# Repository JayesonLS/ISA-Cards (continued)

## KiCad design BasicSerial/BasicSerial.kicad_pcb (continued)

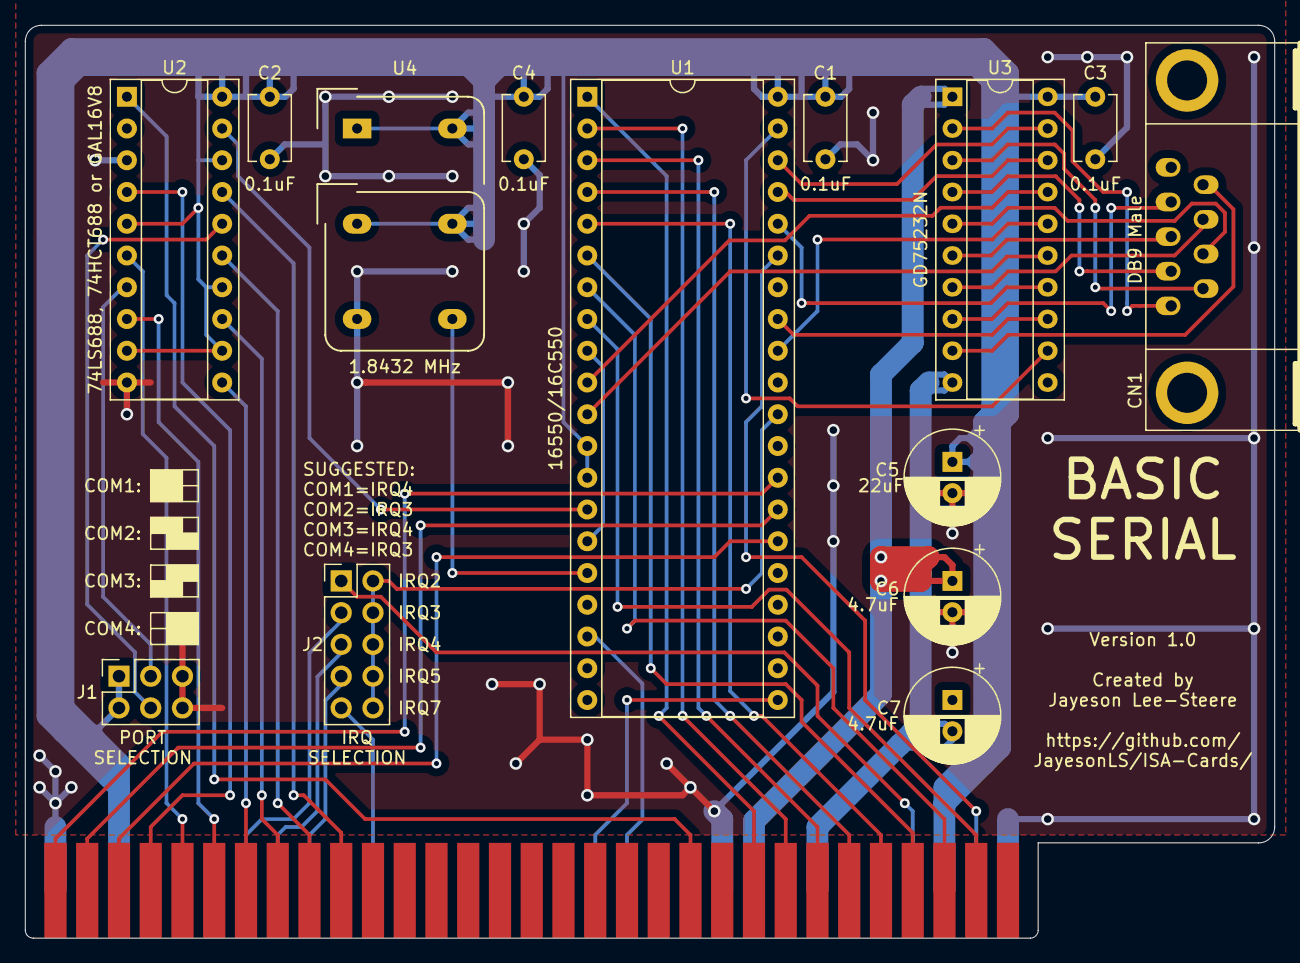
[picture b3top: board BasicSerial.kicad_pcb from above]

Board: 2 copper layers, 99.9 x 73.0 mm, 15 parts (0 on the bottom side), 53 nets.

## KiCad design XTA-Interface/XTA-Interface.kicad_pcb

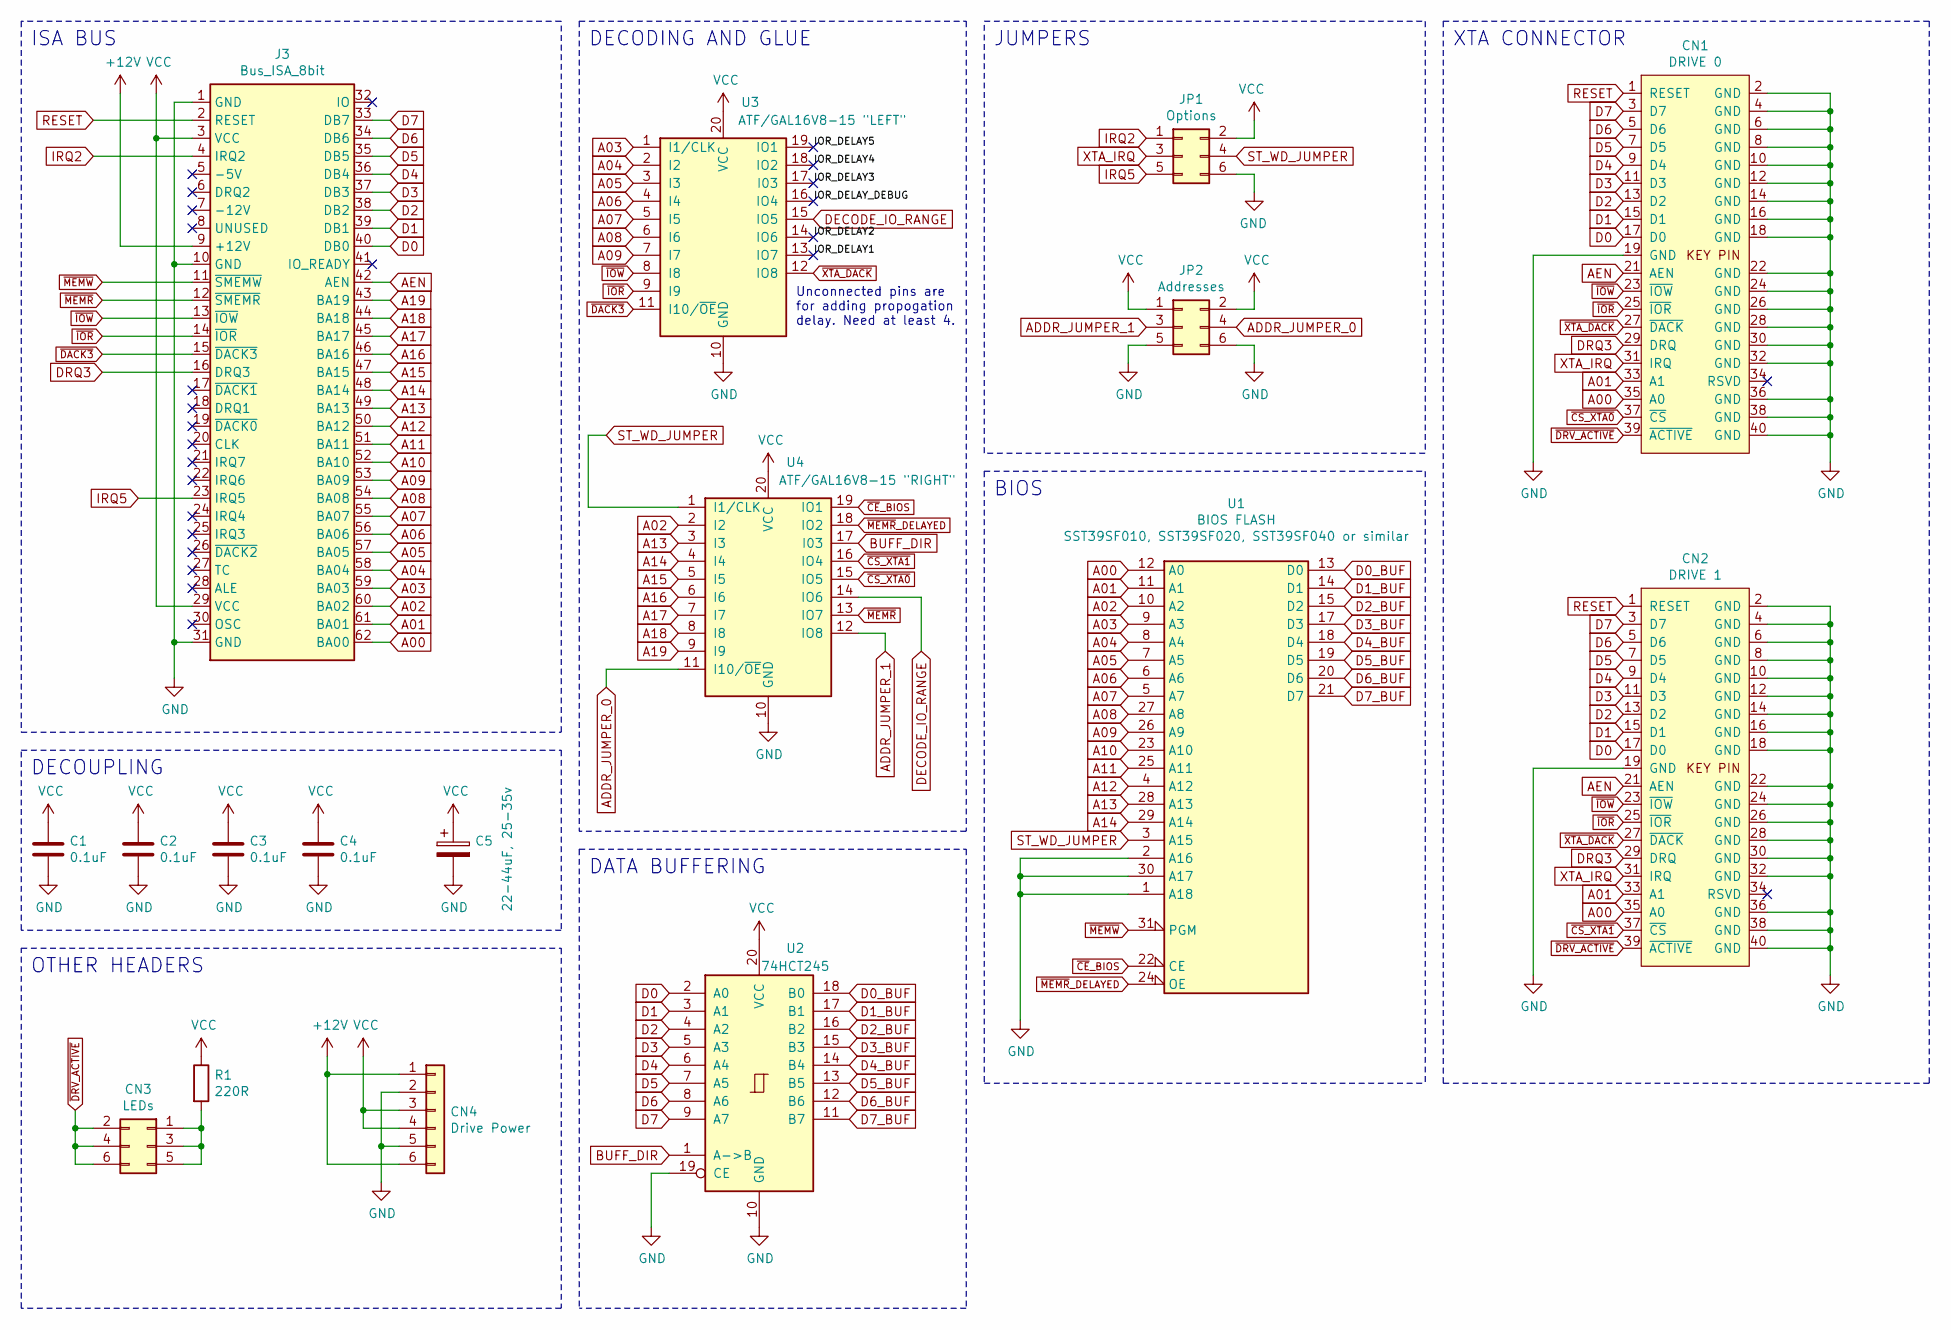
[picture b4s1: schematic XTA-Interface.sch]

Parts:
C1, C2, C3, C4: 0.1uF; C_1206_3216Metric; Part options C84772,C263183; LCSC C84772
C5: 22-44uF, 25-35v; CP_EIA-3528-15_AVX-H
CN1: DRIVE 0; PinHeader_2x20_P2.54mm_Vertical
CN2: DRIVE 1; PinHeader_2x20_P2.54mm_Vertical
CN3: LEDs; PinHeader_2x03_P2.54mm_Vertical
CN4: Drive Power; PinHeader_1x06_P2.54mm_Horizontal
J3: Bus_ISA_8bit; BUS_XT
JP1: Options; PinHeader_2x03_P2.54mm_Vertical
JP2: Addresses; PinHeader_2x03_P2.54mm_Vertical
R1: 220R; R_1206_3216Metric
U1: BIOS FLASH; DIP-32_W15.24mm_Socket
U2: 74HCT245; DIP-20_W7.62mm_Socket
U3: ATF/GAL16V8-15 \"LEFT\"; DIP-20_W7.62mm_Socket
U4: ATF/GAL16V8-15 \"RIGHT\"; DIP-20_W7.62mm_Socket

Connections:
+12V: CN4.1, CN4.6, J3.9 (+12V)
/IOR_DELAY1: U3.13 (IO7)
/IOR_DELAY2: U3.14 (IO6)
/IOR_DELAY3: U3.17 (I03)
/IOR_DELAY4: U3.18 (IO2)
/IOR_DELAY5: U3.19 (IO1)
/IOR_DELAY_DEBUG: U3.16 (IO4)
A00: CN1.35 (A0), CN2.35 (A0), J3.62 (BA00), U1.12 (A0)
A01: CN1.33 (A1), CN2.33 (A1), J3.61 (BA01), U1.11 (A1)
A02: J3.60 (BA02), U1.10 (A2), U4.2 (I2)
A03: J3.59 (BA03), U1.9 (A3), U3.1 (I1/CLK)
A04: J3.58 (BA04), U1.8 (A4), U3.2 (I2)
A05: J3.57 (BA05), U1.7 (A5), U3.3 (I3)
A06: J3.56 (BA06), U1.6 (A6), U3.4 (I4)
A07: J3.55 (BA07), U1.5 (A7), U3.5 (I5)
A08: J3.54 (BA08), U1.27 (A8), U3.6 (I6)
A09: J3.53 (BA09), U1.26 (A9), U3.7 (I7)
A10: J3.52 (BA10), U1.23 (A10)
A11: J3.51 (BA11), U1.25 (A11)
A12: J3.50 (BA12), U1.4 (A12)
A13: J3.49 (BA13), U1.28 (A13), U4.3 (I3)
A14: J3.48 (BA14), U1.29 (A14), U4.4 (I4)
A15: J3.47 (BA15), U4.5 (I5)
A16: J3.46 (BA16), U4.6 (I6)
A17: J3.45 (BA17), U4.7 (I7)
A18: J3.44 (BA18), U4.8 (I8)
A19: J3.43 (BA19), U4.9 (I9)
ADDR_JUMPER_0: JP2.4, U4.11 (I10/~OE~)
ADDR_JUMPER_1: JP2.3, U4.12 (IO8)
AEN: CN1.21 (AEN), CN2.21 (AEN), J3.42 (AEN)
BUFF_DIR: U2.1 (A->B), U4.17 (I03)
D0: CN1.17 (D0), CN2.17 (D0), J3.40 (DB0), U2.2 (A0)
D0_BUF: U1.13 (D0), U2.18 (B0)
D1: CN1.15 (D1), CN2.15 (D1), J3.39 (DB1), U2.3 (A1)
D1_BUF: U1.14 (D1), U2.17 (B1)
D2: CN1.13 (D2), CN2.13 (D2), J3.38 (DB2), U2.4 (A2)
D2_BUF: U1.15 (D2), U2.16 (B2)
D3: CN1.11 (D3), CN2.11 (D3), J3.37 (DB3), U2.5 (A3)
D3_BUF: U1.17 (D3), U2.15 (B3)
D4: CN1.9 (D4), CN2.9 (D4), J3.36 (DB4), U2.6 (A4)
D4_BUF: U1.18 (D4), U2.14 (B4)
D5: CN1.7 (D5), CN2.7 (D5), J3.35 (DB5), U2.7 (A5)
D5_BUF: U1.19 (D5), U2.13 (B5)
D6: CN1.5 (D6), CN2.5 (D6), J3.34 (DB6), U2.8 (A6)
D6_BUF: U1.20 (D6), U2.12 (B6)
D7: CN1.3 (D7), CN2.3 (D7), J3.33 (DB7), U2.9 (A7)
D7_BUF: U1.21 (D7), U2.11 (B7)
DECODE_IO_RANGE: U3.15 (IO5), U4.14 (IO6)
DRQ3: CN1.29 (DRQ), CN2.29 (DRQ), J3.16 (DRQ3)
GND: C1.2, C2.2, C3.2, C4.2, C5.2, CN1.2 (GND), CN1.4 (GND), CN1.6 (GND), CN1.8 (GND), CN1.10 (GND), CN1.12 (GND), CN1.14 (GND), CN1.16 (GND), CN1.18 (GND), CN1.19 (GND), CN1.22 (GND), CN1.24 (GND), CN1.26 (GND), CN1.28 (GND), CN1.30 (GND), CN1.32 (GND), CN1.36 (GND), CN1.38 (GND), CN1.40 (GND), CN2.2 (GND), CN2.4 (GND), CN2.6 (GND), CN2.8 (GND), CN2.10 (GND), CN2.12 (GND), CN2.14 (GND), CN2.16 (GND), CN2.18 (GND), CN2.19 (GND), CN2.22 (GND), CN2.24 (GND), CN2.26 (GND), CN2.28 (GND), CN2.30 (GND), CN2.32 (GND), CN2.36 (GND), CN2.38 (GND), CN2.40 (GND), CN4.2, CN4.5, J3.1 (GND), J3.10 (GND), J3.31 (GND), JP1.6, JP2.5, JP2.6, U1.1 (A18), U1.2 (A16), U1.16 (GND), U1.30 (A17), U2.10 (GND), U2.19 (CE), U3.10 (GND), U4.10 (GND); also elsewhere on the board
IRQ2: J3.4 (IRQ2), JP1.1
IRQ5: J3.23 (IRQ5), JP1.5
unnamed: CN3.1, CN3.3, CN3.5, R1.2
RESET: CN1.1 (RESET), CN2.1 (RESET), J3.2 (RESET)
ST_WD_JUMPER: JP1.4, U1.3 (A15), U4.1 (I1/CLK)
VCC: C1.1, C2.1, C3.1, C4.1, C5.1, CN4.3, CN4.4, J3.3 (VCC), J3.29 (VCC), JP1.2, JP2.1, JP2.2, R1.1, U1.32 (VCC), U2.20 (VCC), U3.20 (VCC), U4.20 (VCC)
XTA_IRQ: CN1.31 (IRQ), CN2.31 (IRQ), JP1.3
~CE~_BIOS: U1.22 (CE), U4.19 (IO1)
~CS_XTA0: CN1.37 (~CS), U4.15 (IO5)
~CS_XTA1: CN2.37 (~CS), U4.16 (IO4)
~DACK3: J3.15 (~DACK3), U3.11 (I10/~OE~)
~DRV_ACTIVE: CN1.39 (~ACTIVE), CN2.39 (~ACTIVE), CN3.2, CN3.4, CN3.6
~IOR: CN1.25 (~IOR), CN2.25 (~IOR), J3.14 (~IOR), U3.9 (I9)
~IOW: CN1.23 (~IOW), CN2.23 (~IOW), J3.13 (~IOW), U3.8 (I8)
~MEMR: J3.12 (~SMEMR), U4.13 (IO7)
~MEMR~_DELAYED: U1.24 (OE), U4.18 (IO2)
~MEMW: J3.11 (~SMEMW), U1.31 (PGM)
~XTA_DACK: CN1.27 (~DACK), CN2.27 (~DACK), U3.12 (IO8)

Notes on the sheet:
ISA BUS
DECOUPLING
DATA BUFFERING
DECODING AND GLUE
BIOS
XTA CONNECTOR
JUMPERS
OTHER HEADERS
Unconnected pins are for adding propogation delay. Need at least 4.

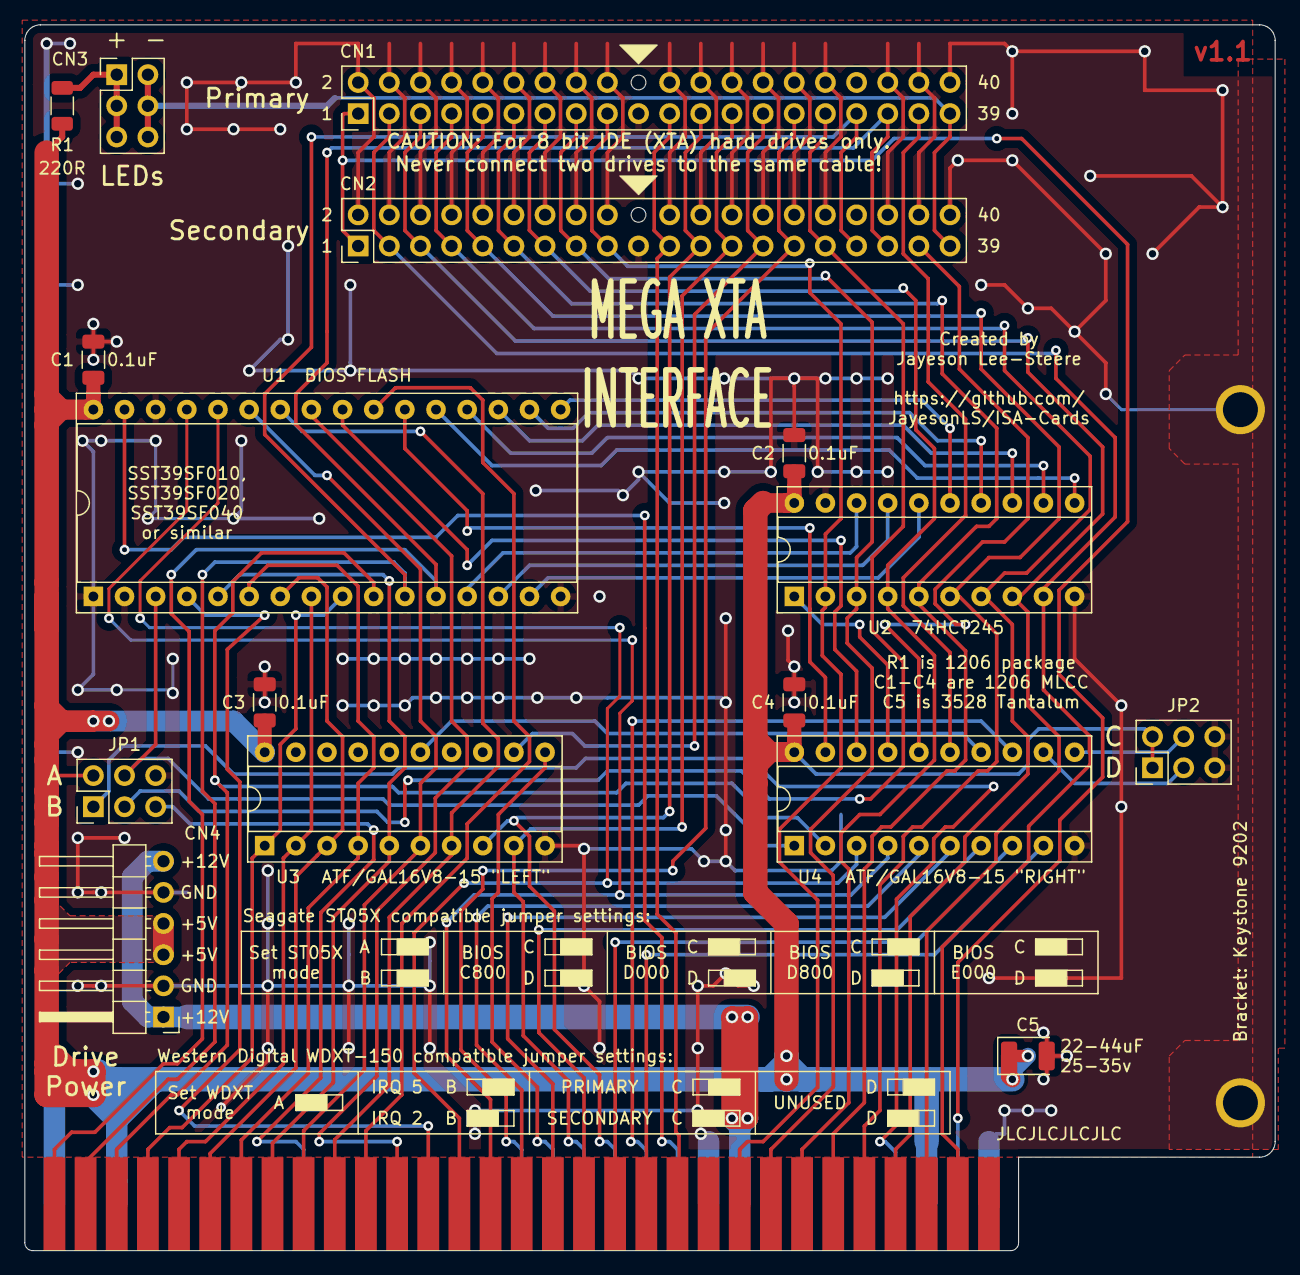
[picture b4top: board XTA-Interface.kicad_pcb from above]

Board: 2 copper layers, 101.9 x 99.9 mm, 19 parts (0 on the bottom side), 62 nets.

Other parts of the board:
H2, H4: MountingHole_Pad; MountingHole_3.5mm_Pad

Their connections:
GND: H2.1, H4.1; also elsewhere on the board

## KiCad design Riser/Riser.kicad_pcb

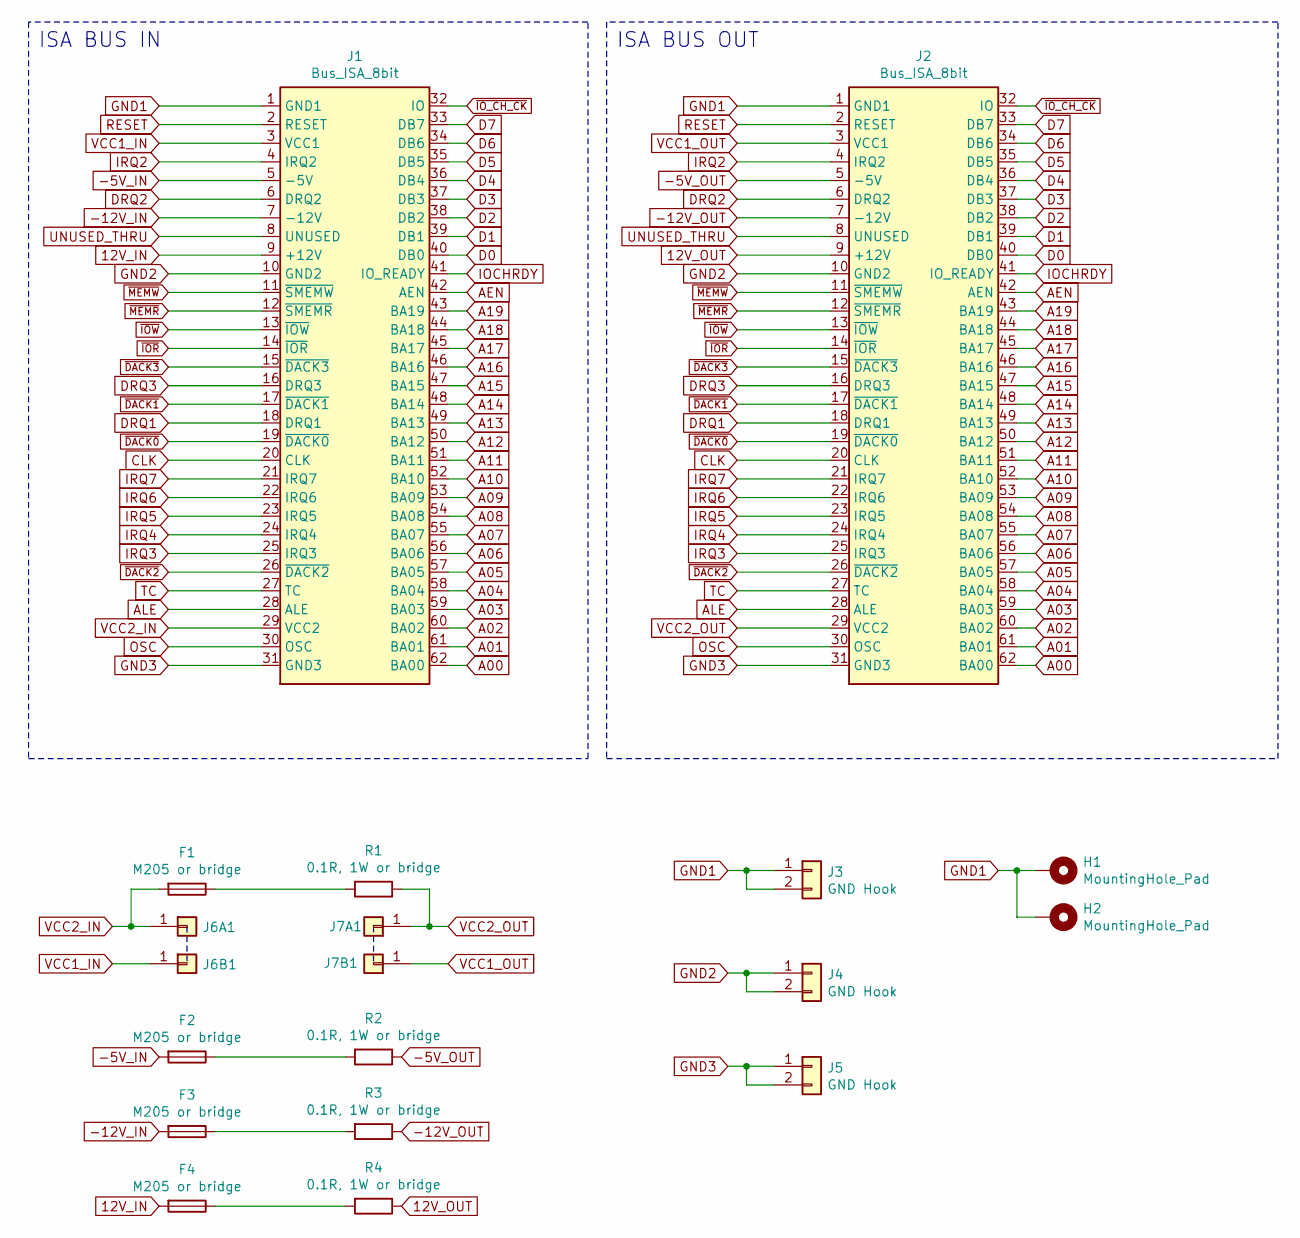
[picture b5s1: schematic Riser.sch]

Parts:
F1, F2, F3, F4: M205 or bridge; Fuseholder5x20_horiz_open_universal_Type-III
H1, H2: MountingHole_Pad; MountingHole_3.5mm_Pad
J1, J2: Bus_ISA_8bit; BUS_XT
J3, J4, J5: GND Hook; GroundHook
J6A1, J6B1, J7A1, J7B1: Conn_01x01; TestPoint_THTPad_D3.0mm_Drill1.5mm
R1, R2, R3, R4: 0.1R, 1W or bridge; R_Axial_DIN0922_L20.0mm_D9.0mm_P30.48mm_Horizontal

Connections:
12V_IN: F4.2, J1.9 (+12V)
12V_OUT: J2.9 (+12V), R4.1
-5V_IN: F2.2, J1.5 (-5V)
-5V_OUT: J2.5 (-5V), R2.1
-12V_IN: F3.2, J1.7 (-12V)
-12V_OUT: J2.7 (-12V), R3.1
A00: J1.62 (BA00), J2.62 (BA00)
A01: J1.61 (BA01), J2.61 (BA01)
A02: J1.60 (BA02), J2.60 (BA02)
A03: J1.59 (BA03), J2.59 (BA03)
A04: J1.58 (BA04), J2.58 (BA04)
A05: J1.57 (BA05), J2.57 (BA05)
A06: J1.56 (BA06), J2.56 (BA06)
A07: J1.55 (BA07), J2.55 (BA07)
A08: J1.54 (BA08), J2.54 (BA08)
A09: J1.53 (BA09), J2.53 (BA09)
A10: J1.52 (BA10), J2.52 (BA10)
A11: J1.51 (BA11), J2.51 (BA11)
A12: J1.50 (BA12), J2.50 (BA12)
A13: J1.49 (BA13), J2.49 (BA13)
A14: J1.48 (BA14), J2.48 (BA14)
A15: J1.47 (BA15), J2.47 (BA15)
A16: J1.46 (BA16), J2.46 (BA16)
A17: J1.45 (BA17), J2.45 (BA17)
A18: J1.44 (BA18), J2.44 (BA18)
A19: J1.43 (BA19), J2.43 (BA19)
AEN: J1.42 (AEN), J2.42 (AEN)
ALE: J1.28 (ALE), J2.28 (ALE)
CLK: J1.20 (CLK), J2.20 (CLK)
D0: J1.40 (DB0), J2.40 (DB0)
D1: J1.39 (DB1), J2.39 (DB1)
D2: J1.38 (DB2), J2.38 (DB2)
D3: J1.37 (DB3), J2.37 (DB3)
D4: J1.36 (DB4), J2.36 (DB4)
D5: J1.35 (DB5), J2.35 (DB5)
D6: J1.34 (DB6), J2.34 (DB6)
D7: J1.33 (DB7), J2.33 (DB7)
DRQ1: J1.18 (DRQ1), J2.18 (DRQ1)
DRQ2: J1.6 (DRQ2), J2.6 (DRQ2)
DRQ3: J1.16 (DRQ3), J2.16 (DRQ3)
GND1: H1.1, H2.1, J1.1 (GND1), J2.1 (GND1), J3.1, J3.2
GND2: J1.10 (GND2), J2.10 (GND2), J4.1, J4.2
GND3: J1.31 (GND3), J2.31 (GND3), J5.1, J5.2
IOCHRDY: J1.41 (IO_READY), J2.41 (IO_READY)
IRQ2: J1.4 (IRQ2), J2.4 (IRQ2)
IRQ3: J1.25 (IRQ3), J2.25 (IRQ3)
IRQ4: J1.24 (IRQ4), J2.24 (IRQ4)
IRQ5: J1.23 (IRQ5), J2.23 (IRQ5)
IRQ6: J1.22 (IRQ6), J2.22 (IRQ6)
IRQ7: J1.21 (IRQ7), J2.21 (IRQ7)
unnamed: F1.1, R1.2
unnamed: F2.1, R2.2
unnamed: F3.1, R3.2
unnamed: F4.1, R4.2
OSC: J1.30 (OSC), J2.30 (OSC)
RESET: J1.2 (RESET), J2.2 (RESET)
TC: J1.27 (TC), J2.27 (TC)
UNUSED_THRU: J1.8 (UNUSED), J2.8 (UNUSED)
VCC1_IN: J1.3 (VCC1), J6B1.1
VCC1_OUT: J2.3 (VCC1), J7B1.1
VCC2_IN: F1.2, J1.29 (VCC2), J6A1.1
VCC2_OUT: J2.29 (VCC2), J7A1.1, R1.1
~DACK0: J1.19 (~DACK0), J2.19 (~DACK0)
~DACK1: J1.17 (~DACK1), J2.17 (~DACK1)
~DACK2: J1.26 (~DACK2), J2.26 (~DACK2)
~DACK3: J1.15 (~DACK3), J2.15 (~DACK3)
~IOR: J1.14 (~IOR), J2.14 (~IOR)
~IOW: J1.13 (~IOW), J2.13 (~IOW)
~IO_CH_CK: J1.32 (IO), J2.32 (IO)
~MEMR: J1.12 (~SMEMR), J2.12 (~SMEMR)
~MEMW: J1.11 (~SMEMW), J2.11 (~SMEMW)

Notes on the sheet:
ISA BUS IN
ISA BUS OUT

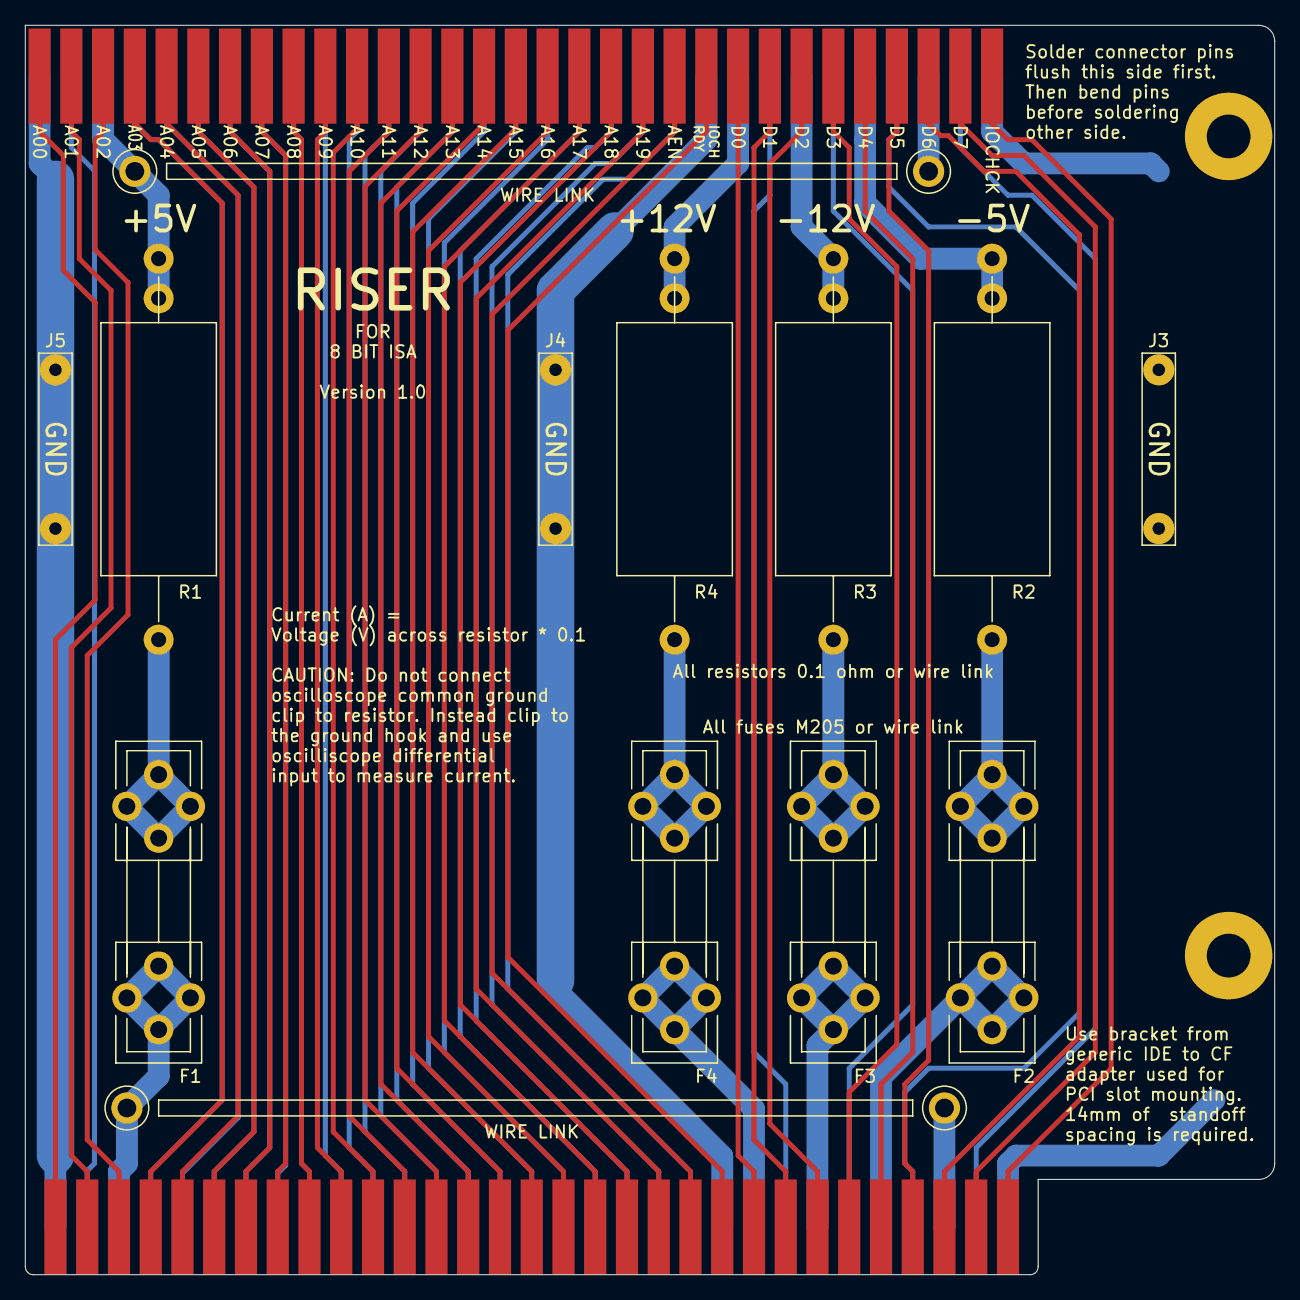
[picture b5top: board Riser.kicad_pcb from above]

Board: 2 copper layers, 99.9 x 99.9 mm, 19 parts (0 on the bottom side), 71 nets.

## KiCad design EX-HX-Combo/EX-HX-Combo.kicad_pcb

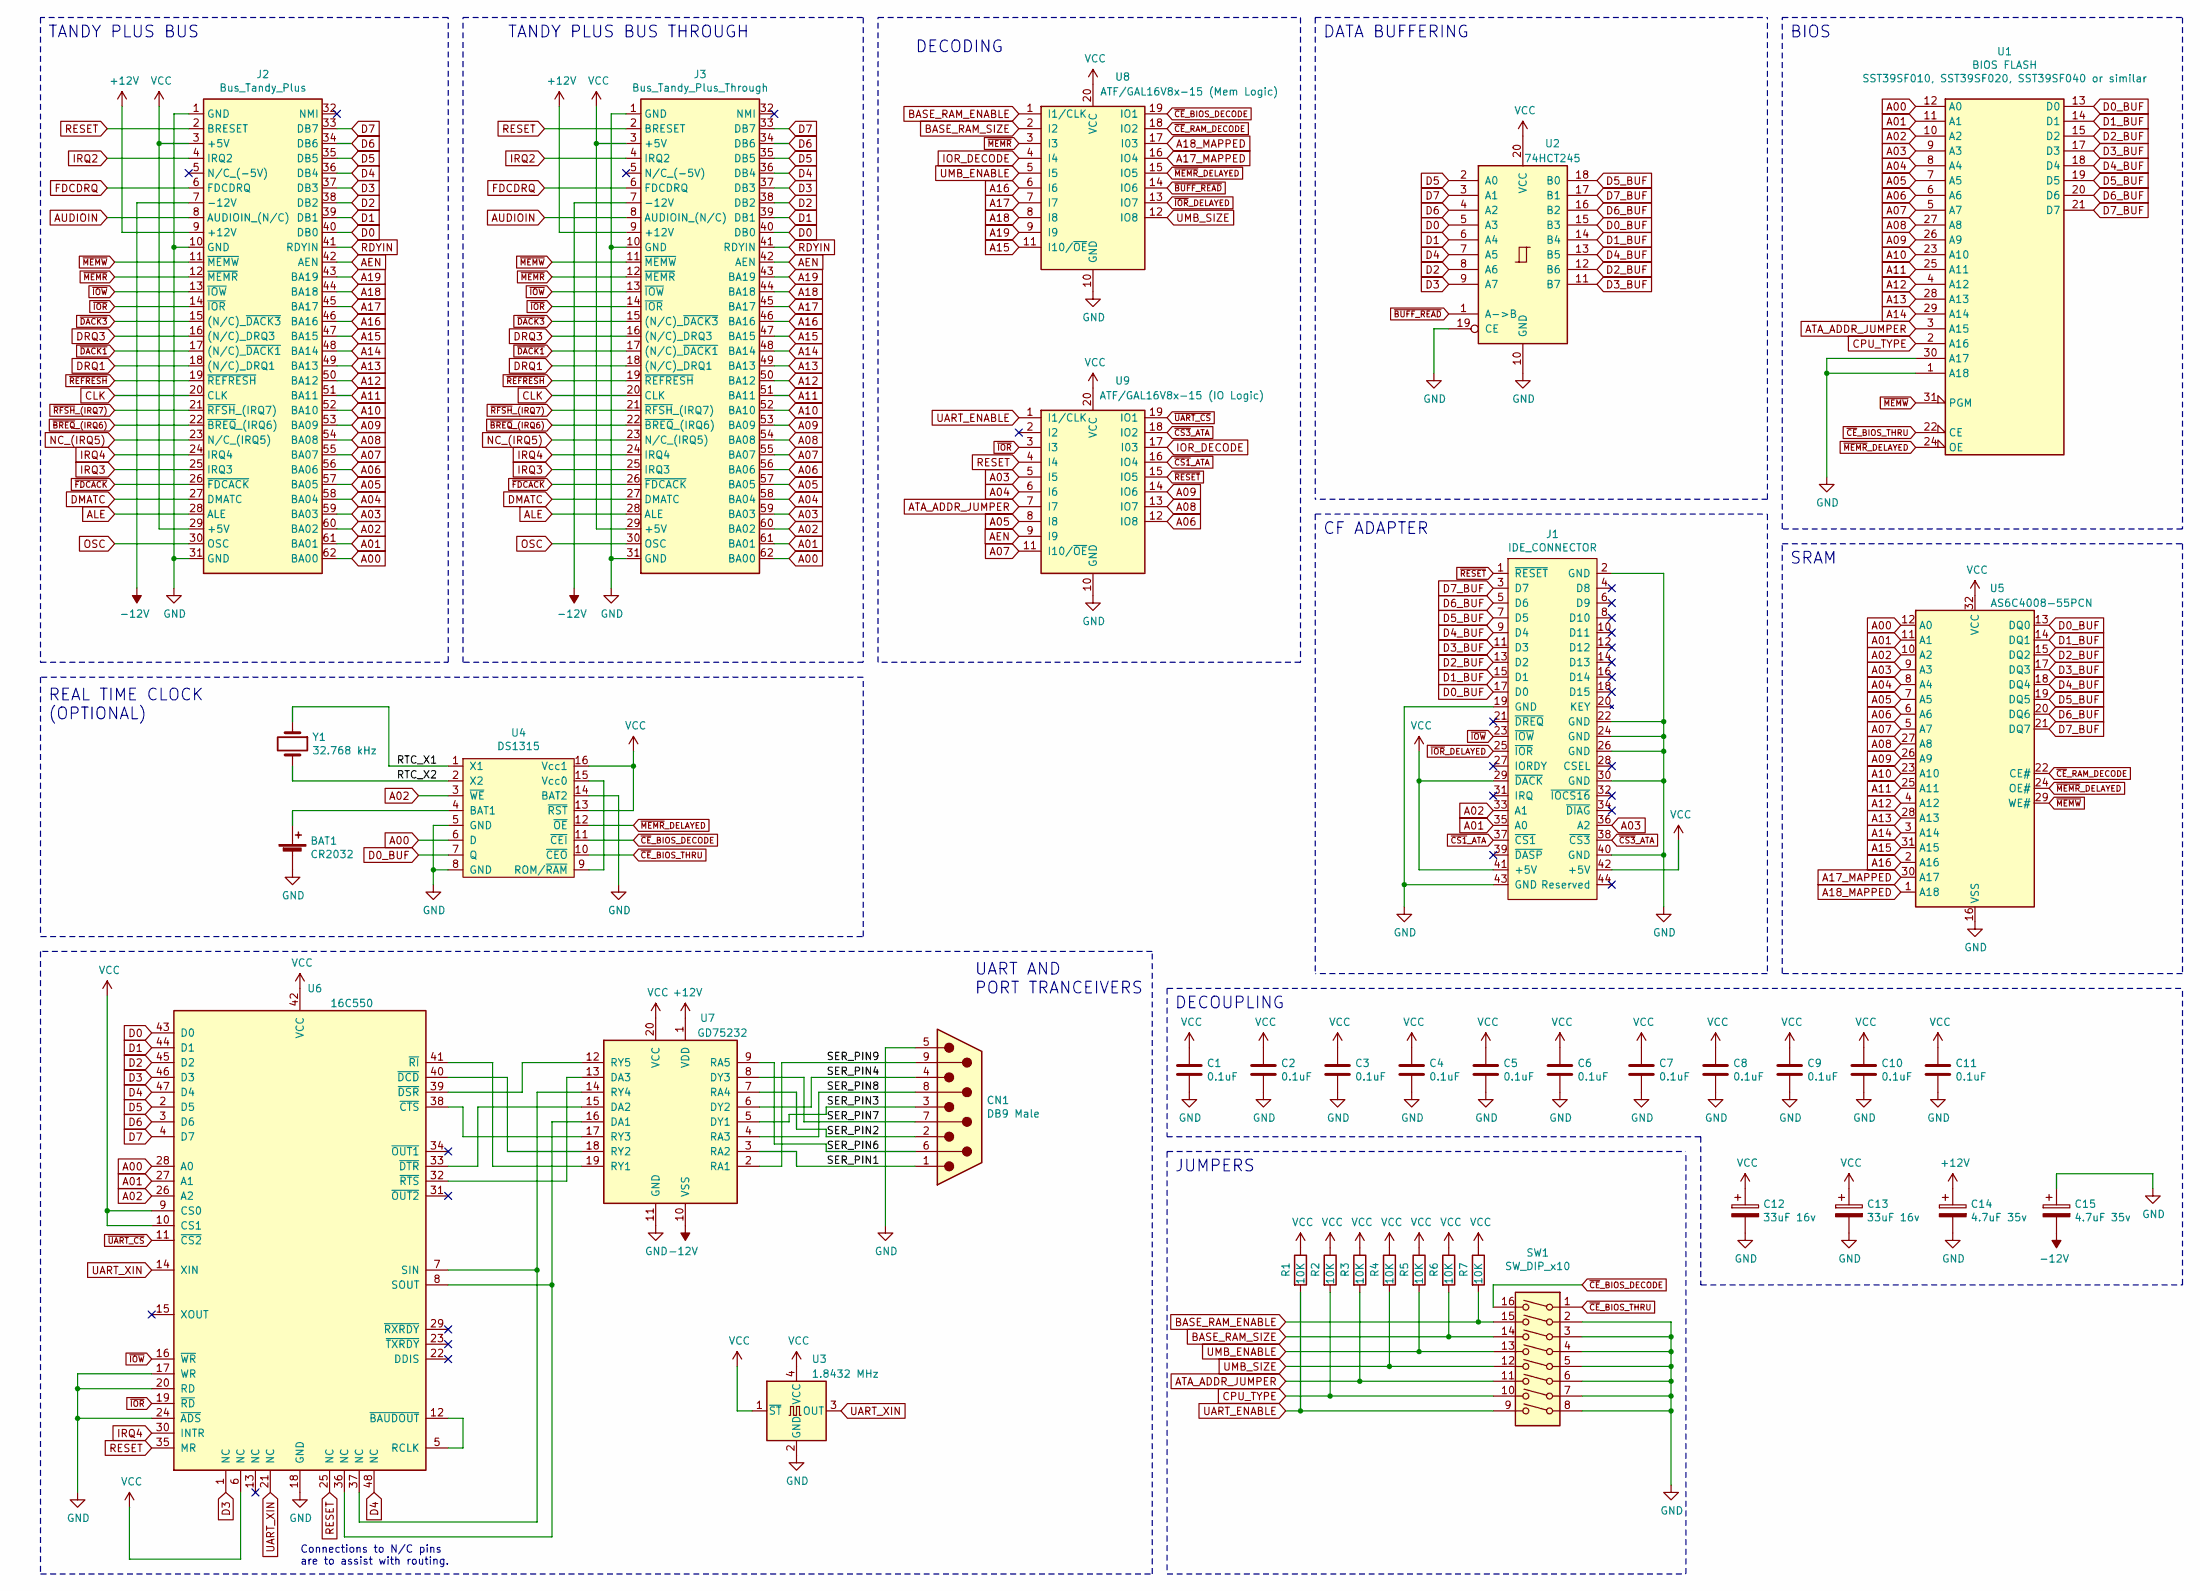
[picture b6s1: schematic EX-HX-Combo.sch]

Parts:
BAT1: CR2032; BatteryHolder_Keystone_1060_1x2032; Part options C964756, C964758, C964764, C964762, C70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; LCSC C964758
C1, C2, C3, C4, C5, C6, C7, C8, C9, C10, C11: 0.1uF; C_1206_3216Metric; LCSC C24497
C12: 33uF 16v; CP_EIA-3528-15_AVX-H; Part options C10785, C125779, C139576; LCSC C10785
C13: 33uF 16v; CP_EIA-3528-15_AVX-H; Part optons C10785, C125779, C139576; LCSC C10785
C14, C15: 4.7uF 35v; CP_EIA-3528-15_AVX-H; Part options C7206, C7201, C506570; LCSC C7206
CN1: DB9 Male; DB_9M
J1: IDE_CONNECTOR; PinSocket_2x22_P2.00mm_Horizontal
J2: Bus_Tandy_Plus; TandyPlusSocket
J3: Bus_Tandy_Plus_Through; TandyPlusSocket
R1, R2, R3, R4, R5, R6, R7: 10K; R_1206_3216Metric; LCSC C17902
SW1: SW_DIP_x10; SW_DIP_SPSTx10_Slide_9.78x27.58mm_W7.62mm_P2.54mm; Part options C99413, C3663, C16160, C319056; LCSC C99413
U1: BIOS FLASH; DIP-32_W15.24mm_Socket; Part options C72122, C146583, C2331; LCSC C146583
U2: 74HCT245; DIP-20_W7.62mm_Socket; Part options C72118, C132507, C2328; LCSC C72118
U3: 1.8432 MHz; Oscillator_SMD_SeikoEpson_SG8002CA-4Pin_7.0x5.0mm; LCSC C386895
U4: DS1315; DIP-16_W7.62mm_Socket; Part options C72115, C146580, C2326; LCSC C72115
U5: AS6C4008-55PCN; DIP-32_W15.24mm_Socket; Part options C72122, C146583, C2331; LCSC C146583
U6: 16C550; LQFP-48_7x7mm_P0.5mm; Part options C181382, C2692304, C84320, C352984; LCSC C181382
U7: GD75232; SOIC-20W_7.5x12.8mm_P1.27mm; LCSC C6662
U8: ATF/GAL16V8x-15 (Mem Logic); DIP-20_W7.62mm_Socket; Part options C72118, C132507, C2328; LCSC C72118
U9: ATF/GAL16V8x-15 (IO Logic); DIP-20_W7.62mm_Socket; Part options C72118, C132507, C2328; LCSC C72118
Y1: 32.768 kHz; Crystal_C38-LF_D3.0mm_L8.0mm_Horizontal; Part options C127496; LCSC C127496

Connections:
+12V: C14.1, J2.9 (+12V), J3.9 (+12V), U7.1 (VDD)
-12V: C15.2, J2.7 (-12V), J3.7 (-12V), U7.10 (VSS)
/RTC_X1: U4.1 (X1), Y1.1
/RTC_X2: U4.2 (X2), Y1.2
/SER_PIN1: CN1.1, U7.3 (RA2)
/SER_PIN2: CN1.2, U7.7 (RA4)
/SER_PIN3: CN1.3, U7.5 (DY1)
/SER_PIN4: CN1.4, U7.6 (DY2)
/SER_PIN6: CN1.6, U7.9 (RA5)
/SER_PIN7: CN1.7, U7.8 (DY3)
/SER_PIN8: CN1.8, U7.4 (RA3)
/SER_PIN9: CN1.9, U7.2 (RA1)
A00: J2.62 (BA00), J3.62 (BA00), U1.12 (A0), U4.6 (D), U5.12 (A0), U6.28 (A0)
A01: J1.35 (A0), J2.61 (BA01), J3.61 (BA01), U1.11 (A1), U5.11 (A1), U6.27 (A1)
A02: J1.33 (A1), J2.60 (BA02), J3.60 (BA02), U1.10 (A2), U4.3 (~WE), U5.10 (A2), U6.26 (A2)
A03: J1.36 (A2), J2.59 (BA03), J3.59 (BA03), U1.9 (A3), U5.9 (A3), U9.5 (I5)
A04: J2.58 (BA04), J3.58 (BA04), U1.8 (A4), U5.8 (A4), U9.6 (I6)
A05: J2.57 (BA05), J3.57 (BA05), U1.7 (A5), U5.7 (A5), U9.8 (I8)
A06: J2.56 (BA06), J3.56 (BA06), U1.6 (A6), U5.6 (A6), U9.12 (IO8)
A07: J2.55 (BA07), J3.55 (BA07), U1.5 (A7), U5.5 (A7), U9.11 (I10/~OE~)
A08: J2.54 (BA08), J3.54 (BA08), U1.27 (A8), U5.27 (A8), U9.13 (IO7)
A09: J2.53 (BA09), J3.53 (BA09), U1.26 (A9), U5.26 (A9), U9.14 (IO6)
A10: J2.52 (BA10), J3.52 (BA10), U1.23 (A10), U5.23 (A10)
A11: J2.51 (BA11), J3.51 (BA11), U1.25 (A11), U5.25 (A11)
A12: J2.50 (BA12), J3.50 (BA12), U1.4 (A12), U5.4 (A12)
A13: J2.49 (BA13), J3.49 (BA13), U1.28 (A13), U5.28 (A13)
A14: J2.48 (BA14), J3.48 (BA14), U1.29 (A14), U5.3 (A14)
A15: J2.47 (BA15), J3.47 (BA15), U5.31 (A15), U8.11 (I10/~OE~)
A16: J2.46 (BA16), J3.46 (BA16), U5.2 (A16), U8.6 (I6)
A17: J2.45 (BA17), J3.45 (BA17), U8.7 (I7)
A17_MAPPED: U5.30 (A17), U8.16 (IO4)
A18: J2.44 (BA18), J3.44 (BA18), U8.8 (I8)
A18_MAPPED: U5.1 (A18), U8.17 (I03)
A19: J2.43 (BA19), J3.43 (BA19), U8.9 (I9)
AEN: J2.42 (AEN), J3.42 (AEN), U9.9 (I9)
ALE: J2.28 (ALE), J3.28 (ALE)
ATA_ADDR_JUMPER: R3.2, SW1.11, U1.3 (A15), U9.7 (I7)
AUDIOIN: J2.8 (AUDIOIN_(N/C)), J3.8 (AUDIOIN_(N/C))
BASE_RAM_ENABLE: R7.2, SW1.15, U8.1 (I1/CLK)
BASE_RAM_SIZE: R6.2, SW1.14, U8.2 (I2)
CLK: J2.20 (CLK), J3.20 (CLK)
CPU_TYPE: R2.2, SW1.10, U1.2 (A16)
D0: J2.40 (DB0), J3.40 (DB0), U2.5 (A3), U6.43 (D0)
D0_BUF: J1.17 (D0), U1.13 (D0), U2.15 (B3), U4.7 (Q), U5.13 (DQ0)
D1: J2.39 (DB1), J3.39 (DB1), U2.6 (A4), U6.44 (D1)
D1_BUF: J1.15 (D1), U1.14 (D1), U2.14 (B4), U5.14 (DQ1)
D2: J2.38 (DB2), J3.38 (DB2), U2.8 (A6), U6.45 (D2)
D2_BUF: J1.13 (D2), U1.15 (D2), U2.12 (B6), U5.15 (DQ2)
D3: J2.37 (DB3), J3.37 (DB3), U2.9 (A7), U6.1 (NC), U6.46 (D3)
D3_BUF: J1.11 (D3), U1.17 (D3), U2.11 (B7), U5.17 (DQ3)
D4: J2.36 (DB4), J3.36 (DB4), U2.7 (A5), U6.47 (D4), U6.48 (NC)
D4_BUF: J1.9 (D4), U1.18 (D4), U2.13 (B5), U5.18 (DQ4)
D5: J2.35 (DB5), J3.35 (DB5), U2.2 (A0), U6.2 (D5)
D5_BUF: J1.7 (D5), U1.19 (D5), U2.18 (B0), U5.19 (DQ5)
D6: J2.34 (DB6), J3.34 (DB6), U2.4 (A2), U6.3 (D6)
D6_BUF: J1.5 (D6), U1.20 (D6), U2.16 (B2), U5.20 (DQ6)
D7: J2.33 (DB7), J3.33 (DB7), U2.3 (A1), U6.4 (D7)
D7_BUF: J1.3 (D7), U1.21 (D7), U2.17 (B1), U5.21 (DQ7)
DMATC: J2.27 (DMATC), J3.27 (DMATC)
DRQ1: J2.18 ((N/C)_DRQ1), J3.18 ((N/C)_DRQ1)
DRQ3: J2.16 ((N/C)_DRQ3), J3.16 ((N/C)_DRQ3)
FDCDRQ: J2.6 (FDCDRQ), J3.6 (FDCDRQ)
GND: BAT1.2 (-), C1.2, C2.2, C3.2, C4.2, C5.2, C6.2, C7.2, C8.2, C9.2, C10.2, C11.2, C12.2, C13.2, C14.2, C15.1, CN1.5, J1.2 (GND), J1.19 (GND), J1.22 (GND), J1.24 (GND), J1.26 (GND), J1.30 (GND), J1.40 (GND), J1.43 (GND), J2.1 (GND), J2.10 (GND), J2.31 (GND), J3.1 (GND), J3.10 (GND), J3.31 (GND), SW1.2, SW1.3, SW1.4, SW1.5, SW1.6, SW1.7, SW1.8, U1.1 (A18), U1.16 (GND), U1.30 (A17), U2.10 (GND), U2.19 (CE), U3.2 (GND), U4.5 (GND), U4.8 (GND), U4.14 (BAT2), U5.16 (VSS), U6.17 (WR), U6.18 (GND), U6.20 (RD), U6.24 (~ADS~), U7.11 (GND), U8.10 (GND), U9.10 (GND)
IOR_DECODE: U8.4 (I4), U9.17 (I03)
IRQ2: J2.4 (IRQ2), J3.4 (IRQ2)
IRQ3: J2.25 (IRQ3), J3.25 (IRQ3)
IRQ4: J2.24 (IRQ4), J3.24 (IRQ4), U6.30 (INTR)
NC_(IRQ5): J2.23 (N/C_(IRQ5)), J3.23 (N/C_(IRQ5))
unnamed: BAT1.1 (+), U4.4 (BAT1)
unnamed: U4.9 (ROM/~RAM), U4.15 (Vcc0)
unnamed: U6.5 (RCLK), U6.12 (~BAUDOUT~)
unnamed: U6.32 (~RTS~), U7.13 (DA3)
unnamed: U6.33 (~DTR~), U7.15 (DA2)
unnamed: U6.8 (SOUT), U6.36 (NC), U7.16 (DA1)
unnamed: U6.7 (SIN), U6.37 (NC), U7.14 (RY4)
unnamed: U6.38 (~CTS~), U7.17 (RY3)
unnamed: U6.39 (~DSR~), U7.12 (RY5)
unnamed: U6.40 (~DCD~), U7.18 (RY2)
unnamed: U6.41 (~RI~), U7.19 (RY1)
OSC: J2.30 (OSC), J3.30 (OSC)
RDYIN: J2.41 (RDYIN), J3.41 (RDYIN)
RESET: J2.2 (BRESET), J3.2 (BRESET), U6.25 (NC), U6.35 (MR), U9.4 (I4)
UART_ENABLE: R1.2, SW1.9, U9.1 (I1/CLK)
UART_XIN: U3.3 (OUT), U6.14 (XIN), U6.21 (NC)
UMB_ENABLE: R5.2, SW1.13, U8.5 (I5)
UMB_SIZE: R4.2, SW1.12, U8.12 (IO8)
VCC: C1.1, C2.1, C3.1, C4.1, C5.1, C6.1, C7.1, C8.1, C9.1, C10.1, C11.1, C12.1, C13.1, J1.29 (~DACK), J1.41 (+5V), J1.42 (+5V), J2.3 (+5V), J2.29 (+5V), J3.3 (+5V), J3.29 (+5V), R1.1, R2.1, R3.1, R4.1, R5.1, R6.1, R7.1, U1.32 (VCC), U2.20 (VCC), U3.1 (~ST), U3.4 (VCC), U4.13 (~RST), U4.16 (Vcc1), U5.32 (VCC), U6.6 (NC), U6.9 (CS0), U6.10 (CS1), U6.42 (VCC), U7.20 (VCC), U8.20 (VCC), U9.20 (VCC)
~BREQ~_(IRQ6): J2.22 (~BREQ~_(IRQ6)), J3.22 (~BREQ~_(IRQ6))
~BUFF_READ: U2.1 (A->B), U8.14 (IO6)
~CE~_BIOS_DECODE: SW1.16, U4.11 (~CEI), U8.19 (IO1)
~CE~_BIOS_THRU: SW1.1, U1.22 (CE), U4.10 (~CEO)
~CE~_RAM_DECODE: U5.22 (CE#), U8.18 (IO2)
~CS1~_ATA: J1.37 (~CS1), U9.16 (IO4)
~CS3~_ATA: J1.38 (~CS3), U9.18 (IO2)
~DACK1: J2.17 ((N/C)_~DACK1), J3.17 ((N/C)_~DACK1)
~DACK3: J2.15 ((N/C)_~DACK3), J3.15 ((N/C)_~DACK3)
~FDCACK: J2.26 (~FDCACK), J3.26 (~FDCACK)
~IOR: J2.14 (~IOR), J3.14 (~IOR), U6.19 (~RD~), U9.3 (I3)
~IOR~_DELAYED: J1.25 (~IOR), U8.13 (IO7)
~IOW: J1.23 (~IOW), J2.13 (~IOW), J3.13 (~IOW), U6.16 (~WR~)
~MEMR: J2.12 (~MEMR), J3.12 (~MEMR), U8.3 (I3)
~MEMR~_DELAYED: U1.24 (OE), U4.12 (~OE), U5.24 (OE#), U8.15 (IO5)
~MEMW: J2.11 (~MEMW), J3.11 (~MEMW), U1.31 (PGM), U5.29 (WE#)
~REFRESH: J2.19 (~REFRESH), J3.19 (~REFRESH)
~RESET: J1.1 (~RESET), U9.15 (IO5)
~RFSH~_(IRQ7): J2.21 (~RFSH~_(IRQ7)), J3.21 (~RFSH~_(IRQ7))
~UART_CS: U6.11 (~CS2~), U9.19 (IO1)

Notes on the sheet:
TANDY PLUS BUS
DECOUPLING
DATA BUFFERING
BIOS
CF ADAPTER
JUMPERS
REAL TIME CLOCK (OPTIONAL)
SRAM
UART AND PORT TRANCEIVERS
DECODING
TANDY PLUS BUS THROUGH
Connections to N/C pins are to assist with routing.
